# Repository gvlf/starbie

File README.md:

# Starbie
A Tamagotchi made by following the tutorial of [SharKingStudios/Starbie](https://github.com/SharKingStudios/Starbie), with minor changes. It's my very first project involving any PCB design work so while this was pretty hard, it was also very enjoyable. 

## render of the PCB

The whole process of making this piece of hardware is written in detail in [JOURNAL.MD](JOURNAL.MD). It took me about 2hrs for the initial setup and making the schematic, the other 4 hours went to the PCB. 

## Photo of the Footprint

## Project status
Only the PCB is finished, I have made Gerber files for printing of the PCB. The BOM will likely be the same as the tutorial one. For the real deal we will have to wait for Week 6 - Building time!  

## Software
The software is literally the same as the tutorial, with the exception that I changed up the SDA and SCL pins on the ESP32 so those are set to 6 and 7 respectively.

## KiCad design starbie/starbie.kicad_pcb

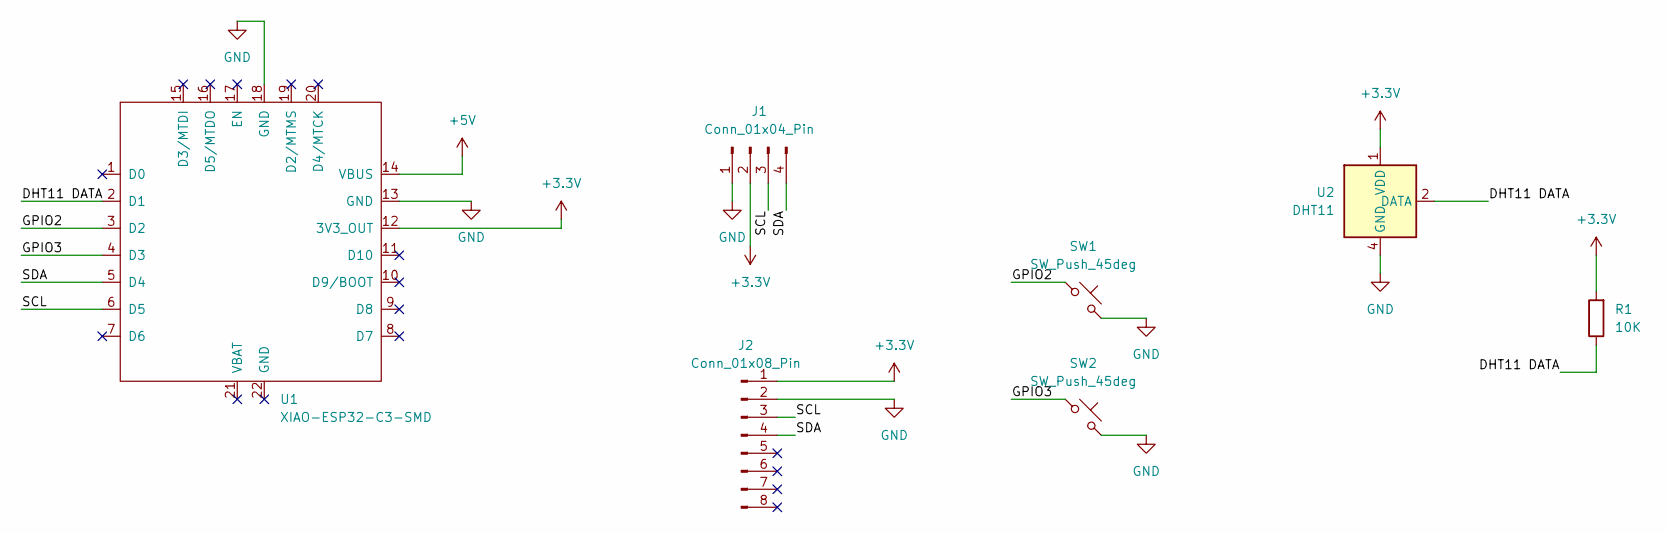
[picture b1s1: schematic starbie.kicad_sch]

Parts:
J1: Conn_01x04_Pin; Display_128x64_096_I2C
J2: Conn_01x08_Pin; PinHeader_1x08_P2.54mm_Vertical
R1: 10K; R_Axial_DIN0204_L3.6mm_D1.6mm_P7.62mm_Horizontal
SW1, SW2: SW_Push_45deg; SW_Cherry_MX_1.00u_PCB
U1: XIAO-ESP32-C3-SMD
U2: DHT11; Aosong_DHT11_5.5x12.0_P2.54mm

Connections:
+3.3V: J1.2, J2.1, R1.2, U1.12 (3V3_OUT), U2.1 (VDD)
+5V: U1.14 (VBUS)
/DHT11 DATA: R1.1, U1.2 (D1), U2.2 (DATA)
/GPIO2: SW1.1, U1.3 (D2)
/GPIO3: SW2.1, U1.4 (D3)
/SCL: J1.3, J2.3, U1.6 (D5)
/SDA: J1.4, J2.4, U1.5 (D4)
GND: J1.1, J2.2, SW1.2, SW2.2, U1.13 (GND), U1.18 (GND), U2.4 (GND)

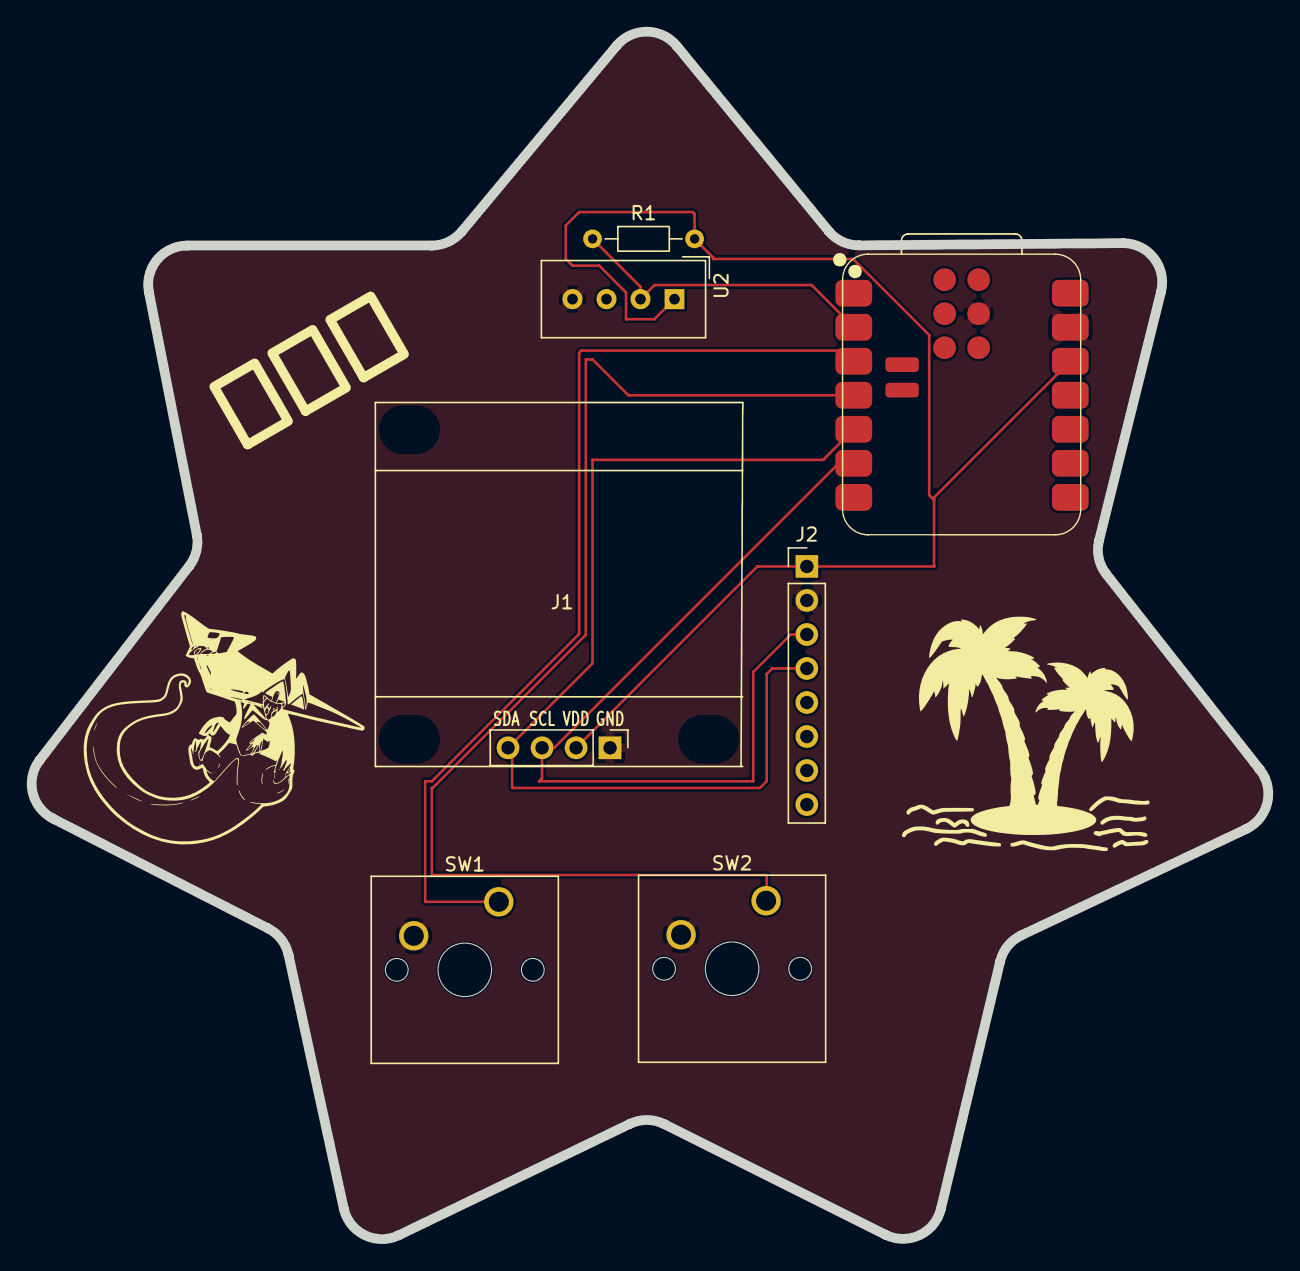
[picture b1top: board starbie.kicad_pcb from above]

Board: 2 copper layers, 92.3 x 90.2 mm, 7 parts (0 on the bottom side), 7 nets.
